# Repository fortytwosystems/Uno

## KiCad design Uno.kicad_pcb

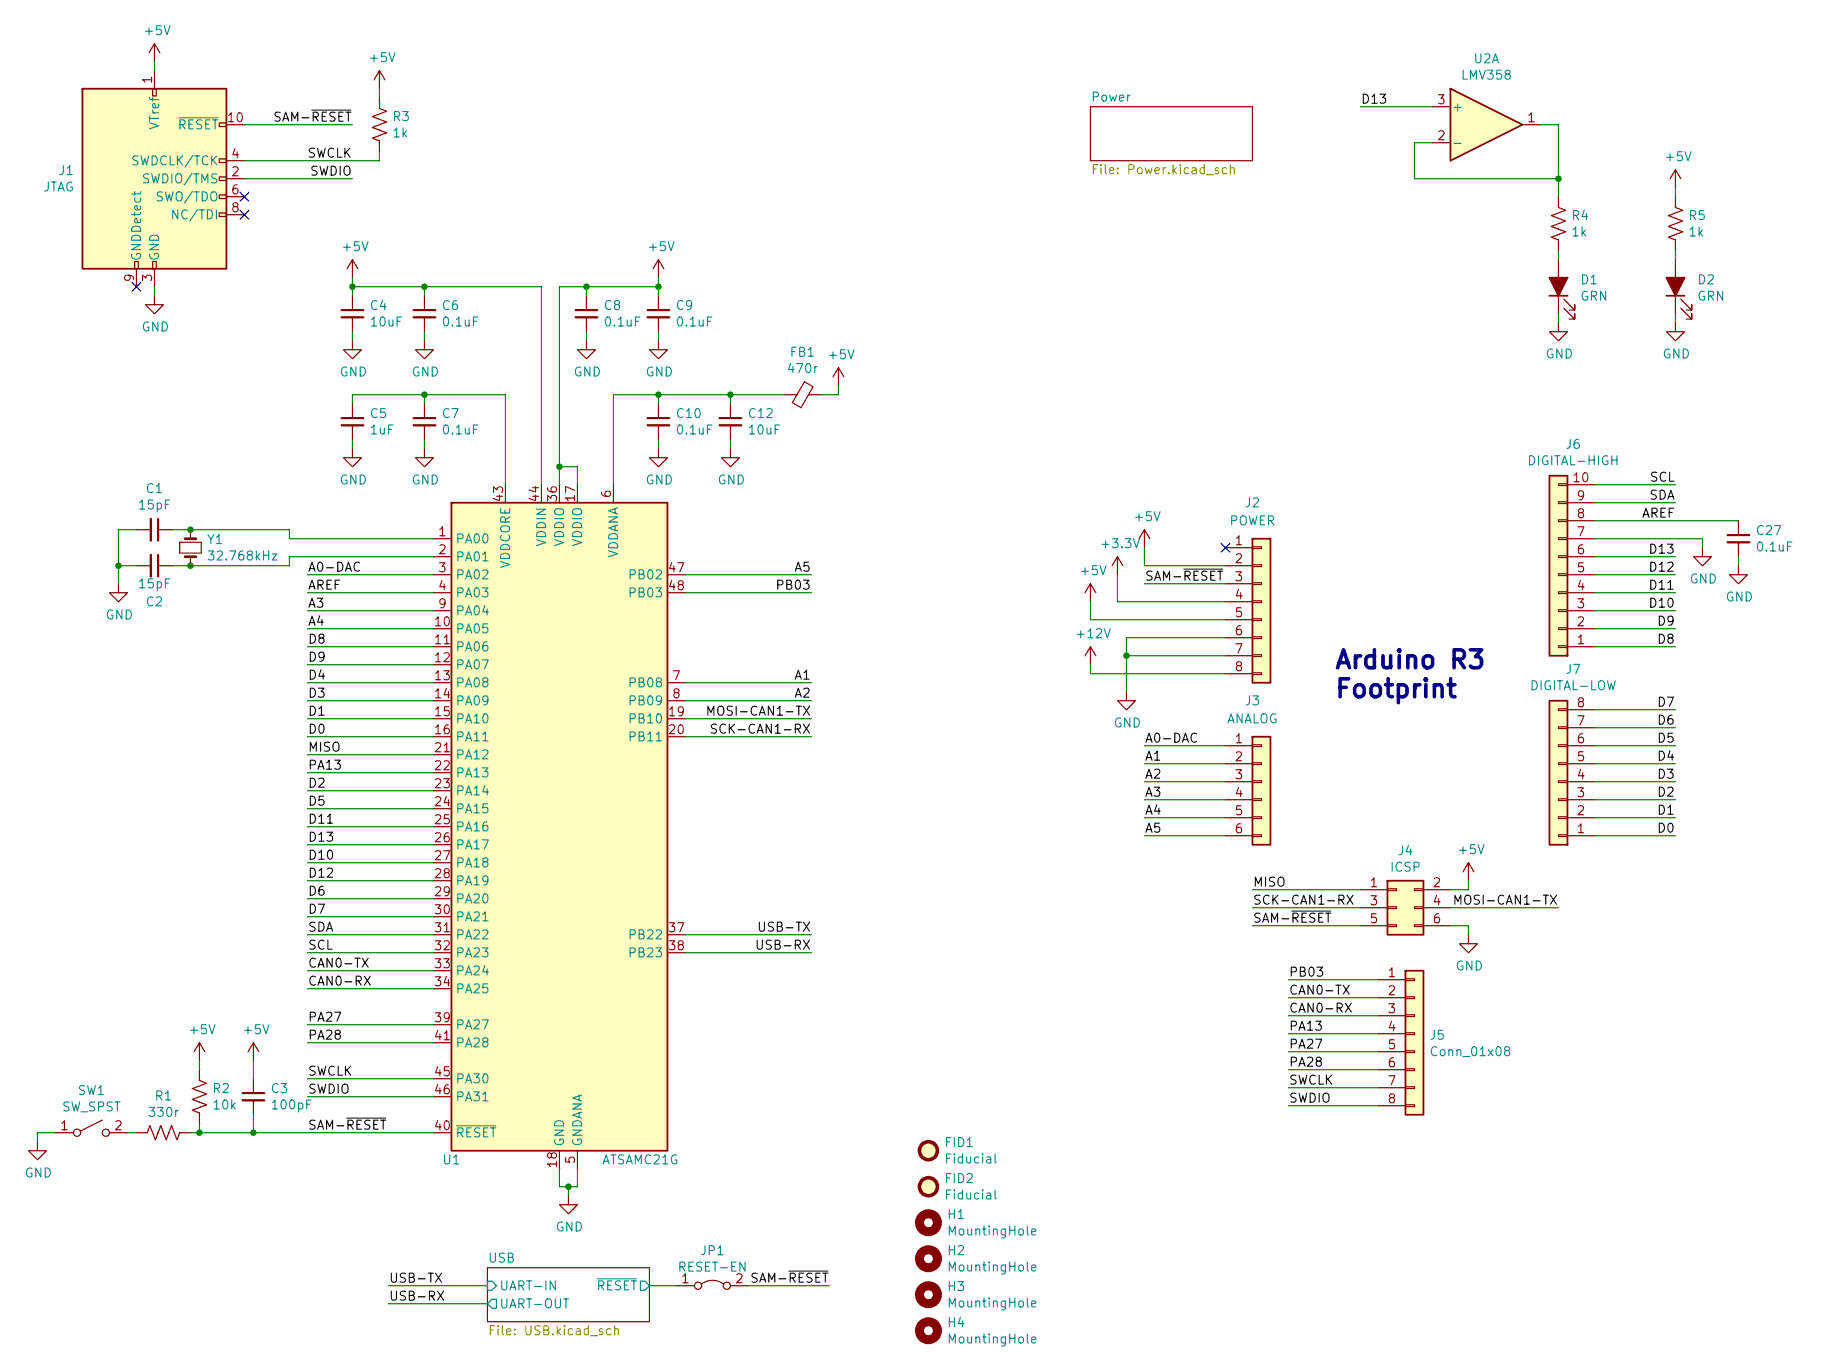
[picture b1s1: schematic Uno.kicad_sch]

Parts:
C1, C2: 15pF; C_0603_1608Metric
C3: 100pF; C_0603_1608Metric
C4, C12: 10uF; C_0805_2012Metric
C5: 1uF; C_0805_2012Metric
C6, C7, C8, C9, C10, C27: 0.1uF; C_0603_1608Metric
D1, D2: GRN; LED_0603_1608Metric
FB1: 470r; R_0603_1608Metric
FID1, FID2: Fiducial; Fiducial_0.75mm_Mask1.5mm
H1, H2, H3, H4: MountingHole; MountingHole_3.2mm_M3
J1: JTAG; PinHeader_2x05_P1.27mm_Vertical
J2: POWER; PinSocket_1x08_P2.54mm_Vertical
J3: ANALOG; PinSocket_1x06_P2.54mm_Vertical
J4: ICSP; PinHeader_2x03_P2.54mm_Vertical
J5: Conn_01x08; PinHeader_1x08_P2.54mm_Vertical
J6: DIGITAL-HIGH; PinSocket_1x10_P2.54mm_Vertical
J7: DIGITAL-LOW; PinSocket_1x08_P2.54mm_Vertical
JP1: RESET-EN; SolderJumper-2_P1.3mm_Bridged_RoundedPad1.0x1.5mm
R1: 330r; R_0603_1608Metric
R2: 10k; R_0603_1608Metric
R3, R4, R5: 1k; R_0603_1608Metric
SW1: SW_SPST; Button-CK-PTS525
U1: ATSAMC21G; TQFP-48_7x7mm_P0.5mm
U2: LMV358; VSSOP-8_3.0x3.0mm_P0.65mm
Y1: 32.768kHz; Crystal_SMD_MicroCrystal_CC7V-T1A-2Pin_3.2x1.5mm

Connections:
+5V: C3.1, C4.1, C6.1, C8.1, C9.1, FB1.1, J1.1 (VTref), J2.2, J2.5, J4.2, R2.2, R3.1, R5.1, U1.17 (VDDIO), U1.36 (VDDIO), U1.44 (VDDIN); also elsewhere on the board
+12V: J2.8; also elsewhere on the board
/A0-DAC: J3.1, U1.3 (PA02)
/A1: J3.2, U1.7 (PB08)
/A2: J3.3, U1.8 (PB09)
/A3: J3.4, U1.9 (PA04)
/A4: J3.5, U1.10 (PA05)
/A5: J3.6, U1.47 (PB02)
/AREF: C27.1, J6.8, U1.4 (PA03)
/CAN0-RX: J5.3, U1.34 (PA25)
/CAN0-TX: J5.2, U1.33 (PA24)
/D0: J7.1, U1.16 (PA11)
/D1: J7.2, U1.15 (PA10)
/D2: J7.3, U1.23 (PA14)
/D3: J7.4, U1.14 (PA09)
/D4: J7.5, U1.13 (PA08)
/D5: J7.6, U1.24 (PA15)
/D6: J7.7, U1.29 (PA20)
/D7: J7.8, U1.30 (PA21)
/D8: J6.1, U1.11 (PA06)
/D9: J6.2, U1.12 (PA07)
/D10: J6.3, U1.27 (PA18)
/D11: J6.4, U1.25 (PA16)
/D12: J6.5, U1.28 (PA19)
/MISO: J4.1, U1.21 (PA12)
/MOSI-CAN1-TX: J4.4, U1.19 (PB10)
/PA13: J5.4, U1.22 (PA13)
/PA27: J5.5, U1.39 (PA27)
/PA28: J5.6, U1.41 (PA28)
/PB03: J5.1, U1.48 (PB03)
/SAM-~RESET~: C3.2, J1.10 (~RESET~), J2.3, J4.5, JP1.2 (B), R1.1, R2.1, U1.40 (~RESET)
/SCK-CAN1-RX: J4.3, U1.20 (PB11)
/SCL: J6.10, U1.32 (PA23)
/SDA: J6.9, U1.31 (PA22)
/SWCLK: J1.4 (SWDCLK/TCK), J5.7, R3.2, U1.45 (PA30)
/SWDIO: J1.2 (SWDIO/TMS), J5.8, U1.46 (PA31)
/USB-RX: U1.38 (PB23); also elsewhere on the board
/USB-TX: U1.37 (PB22); also elsewhere on the board
/USB/~RESET: JP1.1 (A); also elsewhere on the board
GND: C1.2, C2.2, C4.2, C5.2, C6.2, C7.2, C8.2, C9.2, C10.2, C12.2, C27.2, D1.1 (K), D2.1 (K), J1.3 (GND), J1.5 (GND), J2.6, J2.7, J4.6, J6.7, SW1.1 (A), U1.5 (GNDANA), U1.18 (GND), U1.35 (GND), U1.42 (GND); also elsewhere on the board
unnamed: C1.1, U1.1 (PA00), Y1.1
unnamed: C2.1, U1.2 (PA01), Y1.2
unnamed: C5.1, C7.1, U1.43 (VDDCORE)
unnamed: C10.1, C12.1, FB1.2, U1.6 (VDDANA)
unnamed: D1.2 (A), R4.2
unnamed: D2.2 (A), R5.2
unnamed: R1.2, SW1.2 (B)

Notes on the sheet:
Arduino R3 Footprint

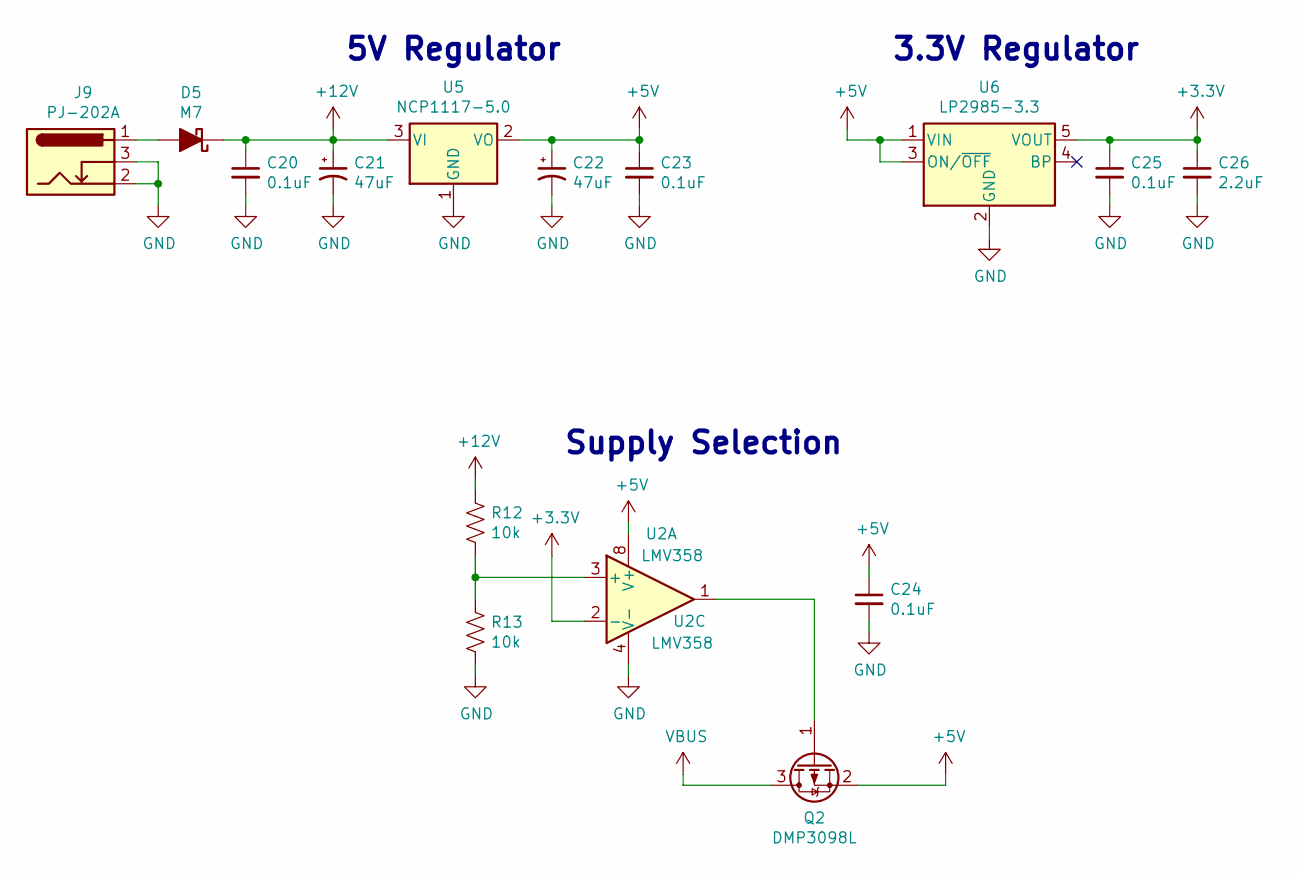
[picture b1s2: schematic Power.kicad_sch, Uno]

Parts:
C20, C23, C24, C25: 0.1uF; C_0603_1608Metric
C21, C22: 47uF; CP_Elec_6.3x5.4
C26: 2.2uF; C_0805_2012Metric
D5: M7; D_SMA
J9: PJ-202A; Barrel-Jack-PJ-202A
Q2: DMP3098L; SOT-23
R12, R13: 10k; R_0603_1608Metric
U2: LMV358; VSSOP-8_3.0x3.0mm_P0.65mm
U5: NCP1117-5.0; SOT-223-3_TabPin2
U6: LP2985-3.3; SOT-23-5

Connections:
+5V: C22.1, C23.1, C24.1, Q2.2 (S), U2.8 (V+), U5.2 (VO), U6.1 (VIN), U6.3 (ON/~OFF~); also elsewhere on the board
+12V: C20.1, C21.1, D5.1 (K), R12.1, U5.3 (VI); also elsewhere on the board
GND: C20.2, C21.2, C22.2, C23.2, C24.2, C25.2, C26.2, J9.2, J9.3, R13.2, U2.4 (V-), U5.1 (GND), U6.2 (GND); also elsewhere on the board
unnamed: D5.2 (A), J9.1
VBUS: Q2.3 (D); also elsewhere on the board

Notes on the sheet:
5V Regulator
Supply Selection
3.3V Regulator

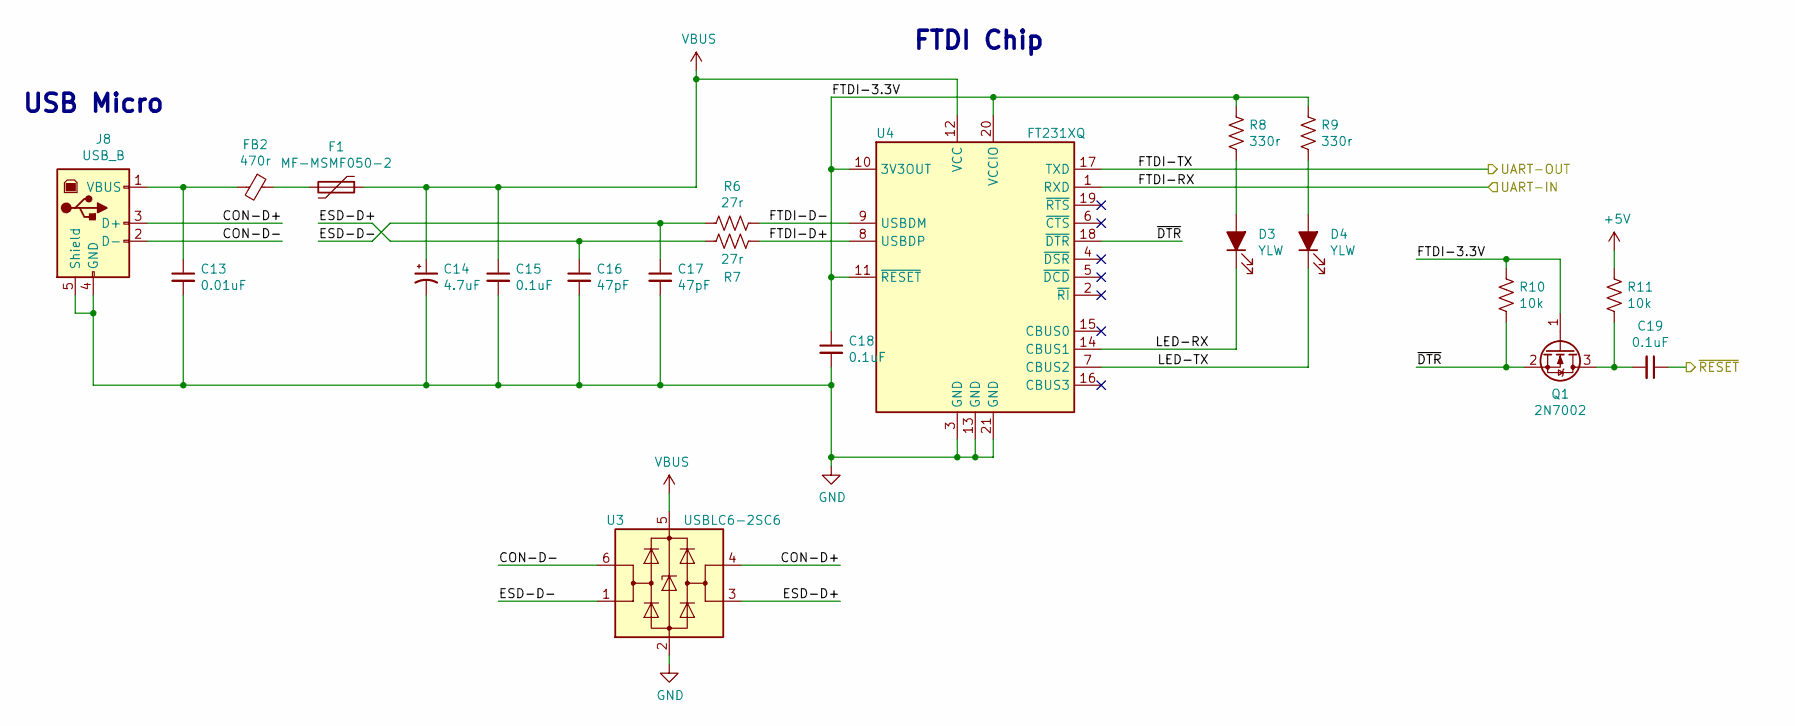
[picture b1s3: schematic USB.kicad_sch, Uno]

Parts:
C13: 0.01uF; C_0603_1608Metric
C14: 4.7uF; CP_EIA-3216-18_Kemet-A
C15, C18, C19: 0.1uF; C_0603_1608Metric
C16, C17: 47pF; C_0603_1608Metric
D3, D4: YLW; LED_0603_1608Metric
F1: MF-MSMF050-2; Fuse_1812_4532Metric
FB2: 470r; R_0603_1608Metric; Part Number BLM18PG471SN1; Digikey PN 490-5223-1-ND
J8: USB_B; USB-B-Amphenol-61729-1011BLF
Q1: 2N7002; SOT-23
R6, R7: 27r; R_0603_1608Metric
R8, R9: 330r; R_0603_1608Metric
R10, R11: 10k; R_0603_1608Metric
U3: USBLC6-2SC6; SOT-23-6
U4: FT231XQ; QFN-20-1EP_4x4mm_P0.5mm_EP2.5x2.5mm

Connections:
+5V: R11.1; also elsewhere on the board
/USB-RX: U4.17 (TXD); also elsewhere on the board
/USB-TX: U4.1 (RXD); also elsewhere on the board
/USB/CON-D+: J8.3 (D+), U3.4 (I/O2)
/USB/CON-D-: J8.2 (D-), U3.6 (I/O1)
/USB/ESD-D+: C16.1, R7.2, U3.3 (I/O2)
/USB/ESD-D-: C17.1, R6.2, U3.1 (I/O1)
/USB/FTDI-3.3V: C18.1, Q1.1 (G), R8.1, R9.1, R10.1, U4.10 (3V3OUT), U4.11 (~RESET), U4.20 (VCCIO)
/USB/FTDI-D+: R7.1, U4.8 (USBDP)
/USB/FTDI-D-: R6.1, U4.9 (USBDM)
/USB/LED-RX: D3.1 (K), U4.14 (CBUS1)
/USB/LED-TX: D4.1 (K), U4.7 (CBUS2)
/USB/~DTR~: Q1.2 (S), R10.2, U4.18 (~DTR)
/USB/~RESET: C19.1; also elsewhere on the board
GND: C13.2, C14.2, C15.2, C16.2, C17.2, C18.2, J8.4 (GND), J8.5 (Shield), U3.2 (GND), U4.3 (GND), U4.13 (GND), U4.21 (GND); also elsewhere on the board
unnamed: C13.1, FB2.2, J8.1 (VBUS)
unnamed: C19.2, Q1.3 (D), R11.2
unnamed: D3.2 (A), R8.2
unnamed: D4.2 (A), R9.2
unnamed: F1.2, FB2.1
VBUS: C14.1, C15.1, F1.1, U3.5 (VBUS), U4.12 (VCC); also elsewhere on the board

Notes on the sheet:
USB Micro
FTDI Chip

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
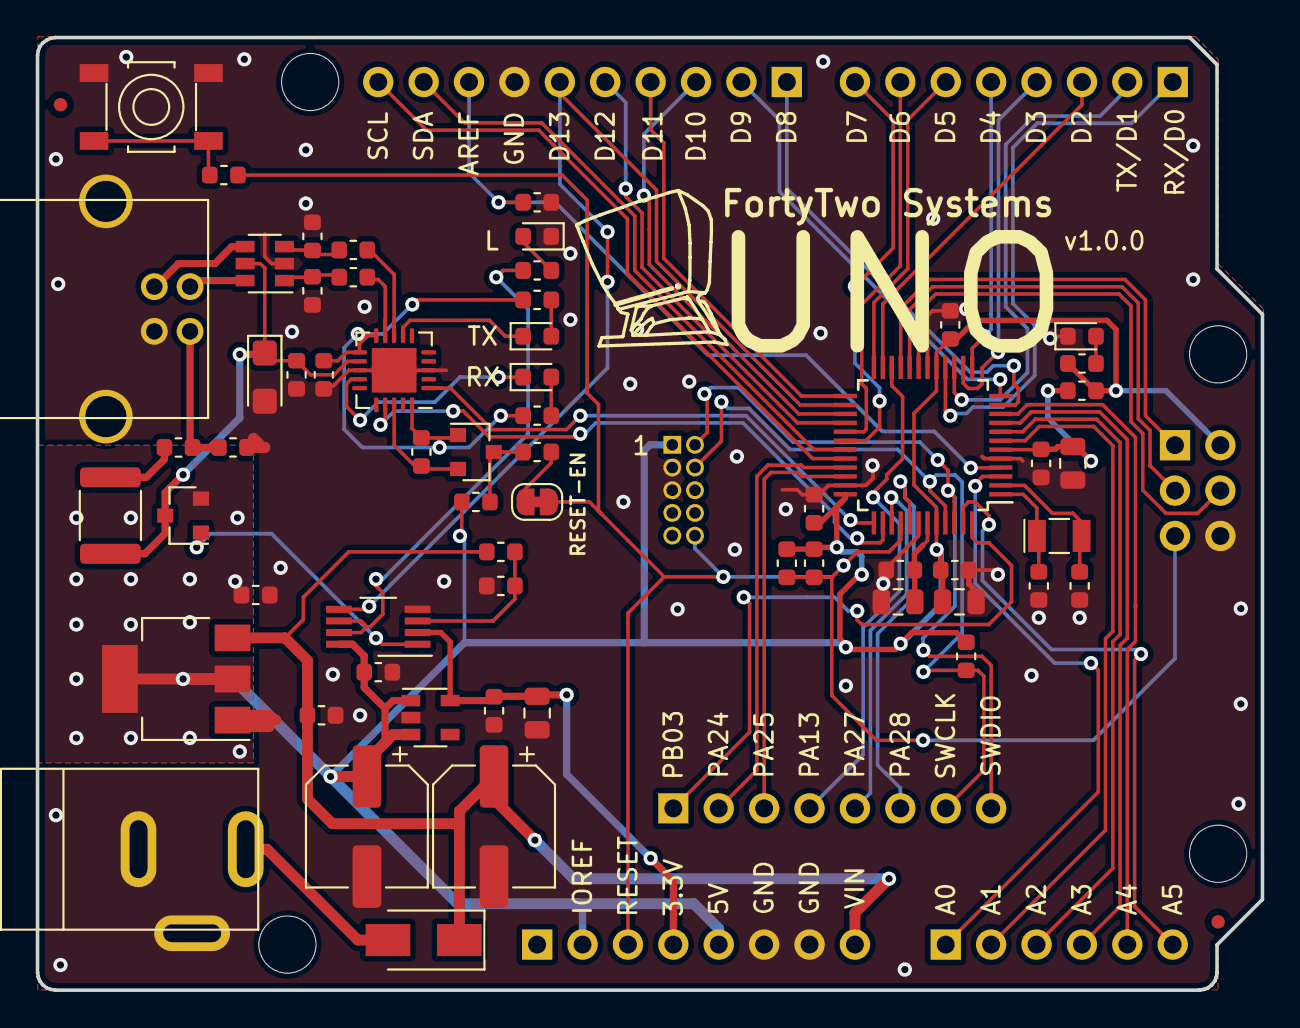
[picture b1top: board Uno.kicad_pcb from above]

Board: 2 copper layers, 68.5 x 53.3 mm, 73 parts (0 on the bottom side), 69 nets.

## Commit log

2021-03-28 Initial GitHub commit
2021-03-28 Create LICENSE
2021-05-04 Move to KiCAD 5.99 and release v1.0.0
2021-05-04 Rename schematics for parity with Mega
